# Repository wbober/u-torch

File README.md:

u-torch
=======

A miniature (2x1cm), high power, LED driver with integrated micro-usb Li-Ion charger.

Features
========
- LTC3454 1A LED driver
- LTC4062 Li-Ion linear charger (from micro-usb)
- Battery cutoff voltage detection
- On/Off switch

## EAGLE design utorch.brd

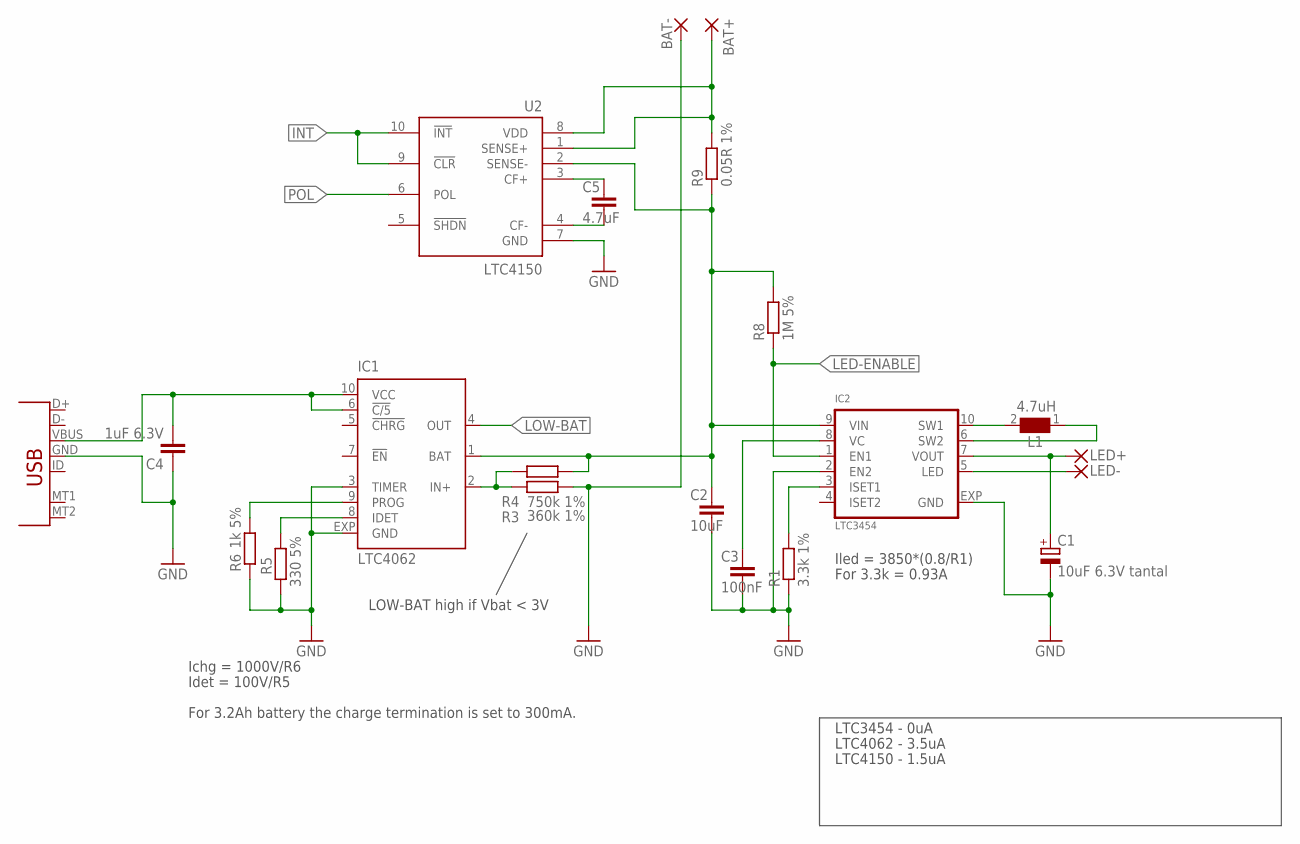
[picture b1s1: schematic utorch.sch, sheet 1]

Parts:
BAT+: WIREPAD1,6/0,8; 1,6/0,8
BAT-: WIREPAD1,6/0,8; 1,6/0,8
C1: 10uF 6.3V tantal; SMC_A
C2: 10uF; C0603
C3: 100nF; ADL_LIB_001_C0402
C4: 1uF 6.3V; ADL_LIB_001_C0402
C5: 4.7uF; C0603
IC1: LTC4062; DFN10-3X3
IC2: LTC3454; DFN10-3X3
L1: 4.7uH; WE-MAPI_2510
LED+: WIREPAD1,6/0,8; 1,6/0,8
LED-: WIREPAD1,6/0,8; 1,6/0,8
R1: 3.3k 1%; ADL_LIB_001_R0402
R3: 360k 1%; ADL_LIB_001_R0402
R4: 750k 1%; ADL_LIB_001_R0402
R5: 330 5%; R0402
R6: 1k 5%; R0402
R8: 1M 5%; ADL_LIB_001_R0402
R9: 0.05R 1%; ADL_LIB_001_R0402
U2: LTC4150; MSOP10
X1: USB-MICROB

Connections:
BAT+: C2.1, IC1.1 (BAT), IC2.9 (VIN), R4.1, R8.2, R9.1, U2.2 (SENSE-)
GND: BAT-.1, C1.-, C2.2, C3.1, C4.1, IC1.3 (TIMER), IC1.EXP (GND), IC2.2 (EN2), IC2.EXP (GND), R1.1, R3.1, R5.1, R6.1, U2.7 (GND), X1.GND; also elsewhere on the board
INT: U2.9 (!CLR!), U2.10 (!INT!); also elsewhere on the board
LED-ENABLE: IC2.1 (EN1), R8.1; also elsewhere on the board
LOW-BAT: IC1.4 (OUT); also elsewhere on the board
unnamed: IC2.10 (SW1), L1.2
unnamed: IC2.6 (SW2), L1.1
unnamed: IC2.5 (LED), LED-.1
unnamed: C1.+, IC2.7 (VOUT), LED+.1
unnamed: IC2.3 (ISET1), R1.2
unnamed: C3.2, IC2.8 (VC)
unnamed: IC1.8 (IDET), R5.2
unnamed: IC1.9 (PROG), R6.2
unnamed: IC1.2 (IN+), R3.2, R4.2
unnamed: C4.2, IC1.6 (!C/5), IC1.10 (VCC), X1.VBUS
unnamed: BAT+.1, R9.2, U2.1 (SENSE+), U2.8 (VDD)
unnamed: C5.2, U2.4 (CF-)
unnamed: C5.1, U2.3 (CF+)
POL: U2.6 (POL); also elsewhere on the board

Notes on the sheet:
Ichg = 1000V/R6
Idet = 100V/R5
For 3.2Ah battery the charge termination is set to 300mA.
Iled = 3850*(0.8/R1)
For 3.3k = 0.93A
LOW-BAT high if Vbat < 3V
LTC3454 - 0uA
LTC4062 - 3.5uA
LTC4150 - 1.5uA

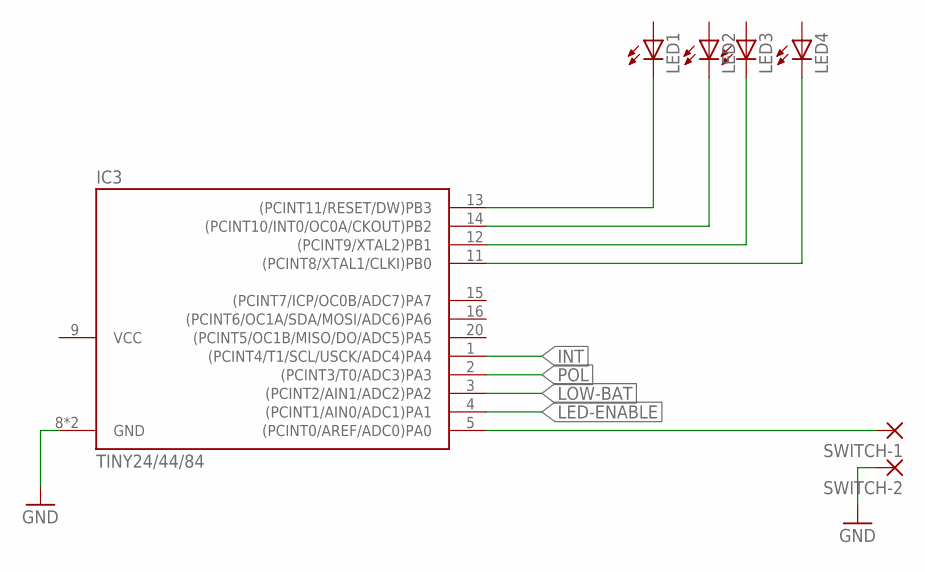
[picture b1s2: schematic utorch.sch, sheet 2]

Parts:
IC3: TINY24/44/84; QFN20-3X3
LED1, LED2, LED3, LED4: LEDCHIPLED_1206; CHIPLED_1206
SWITCH-1, SWITCH-2: WIREPAD1,6/0,8; 1,6/0,8

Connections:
GND: IC3.8 (GND), IC3.EXP (GND), SWITCH-2.1; also elsewhere on the board
INT: IC3.1 ((PCINT4/T1/SCL/USCK/ADC4)PA4); also elsewhere on the board
LED-ENABLE: IC3.4 ((PCINT1/AIN0/ADC1)PA1); also elsewhere on the board
LOW-BAT: IC3.3 ((PCINT2/AIN1/ADC2)PA2); also elsewhere on the board
unnamed: IC3.5 ((PCINT0/AREF/ADC0)PA0), SWITCH-1.1
unnamed: IC3.11 ((PCINT8/XTAL1/CLKI)PB0), LED4.C
unnamed: IC3.12 ((PCINT9/XTAL2)PB1), LED3.C
unnamed: IC3.14 ((PCINT10/INT0/OC0A/CKOUT)PB2), LED2.C
unnamed: IC3.13 ((PCINT11/RESET/DW)PB3), LED1.C
POL: IC3.2 ((PCINT3/T0/ADC3)PA3); also elsewhere on the board
VCC: IC3.9 (VCC)

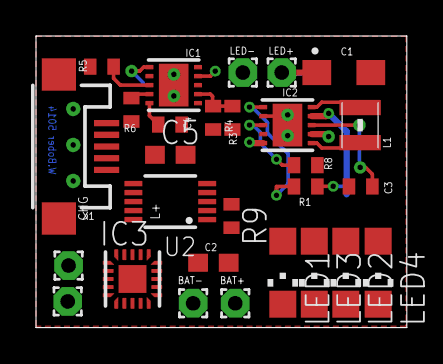
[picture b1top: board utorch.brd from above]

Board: 2 copper layers, 20.6 x 16.2 mm, 28 parts (0 on the bottom side), 24 nets.

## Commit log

2014-12-18 PCB finished
2014-12-22 Fixed on/off logic
2015-01-01 Increased LED traces width to 0.35mm. Added FAB files.
2015-01-23 Fixed ltc4062 enable pin...
2015-01-24 inital update
2015-08-20 something
2015-09-12 Directory cleanup, added photo, upaded readme.md

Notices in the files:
parts and their libraries:
PowerMagnetics: Copyright: Würth Elektronik
adl_lib_001: copyright Alex i Wojtek
